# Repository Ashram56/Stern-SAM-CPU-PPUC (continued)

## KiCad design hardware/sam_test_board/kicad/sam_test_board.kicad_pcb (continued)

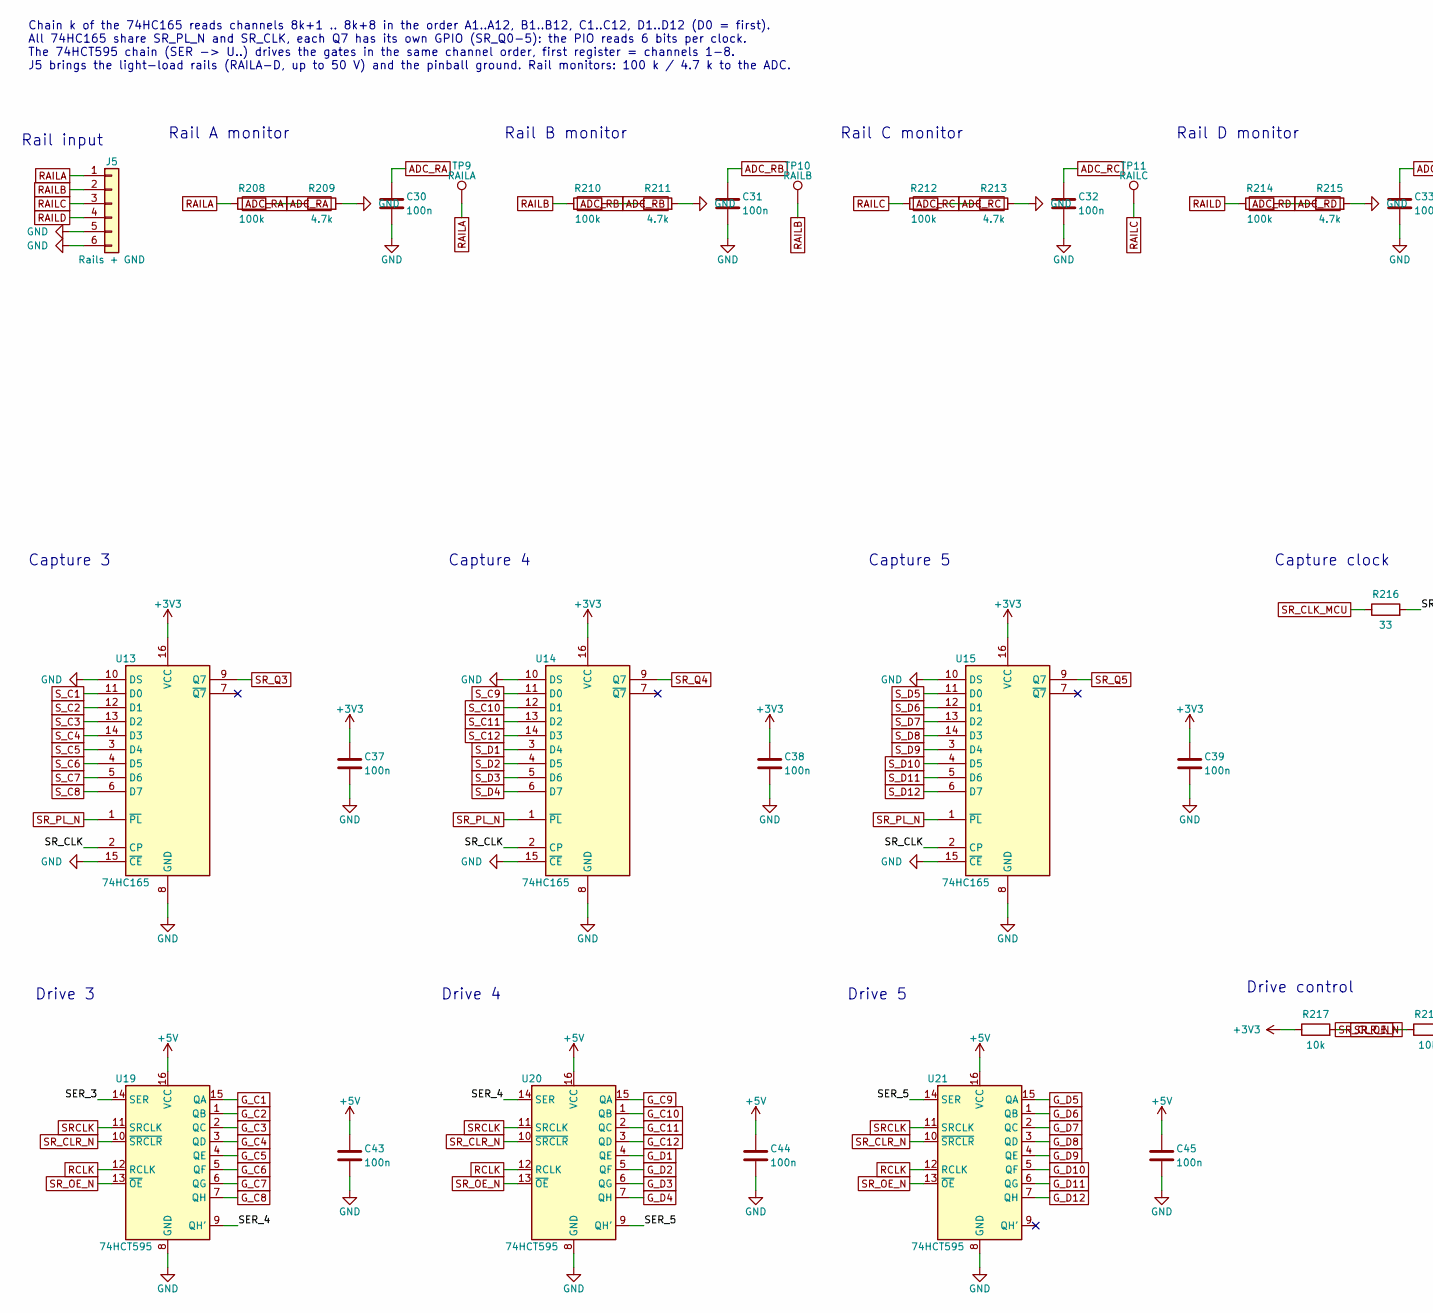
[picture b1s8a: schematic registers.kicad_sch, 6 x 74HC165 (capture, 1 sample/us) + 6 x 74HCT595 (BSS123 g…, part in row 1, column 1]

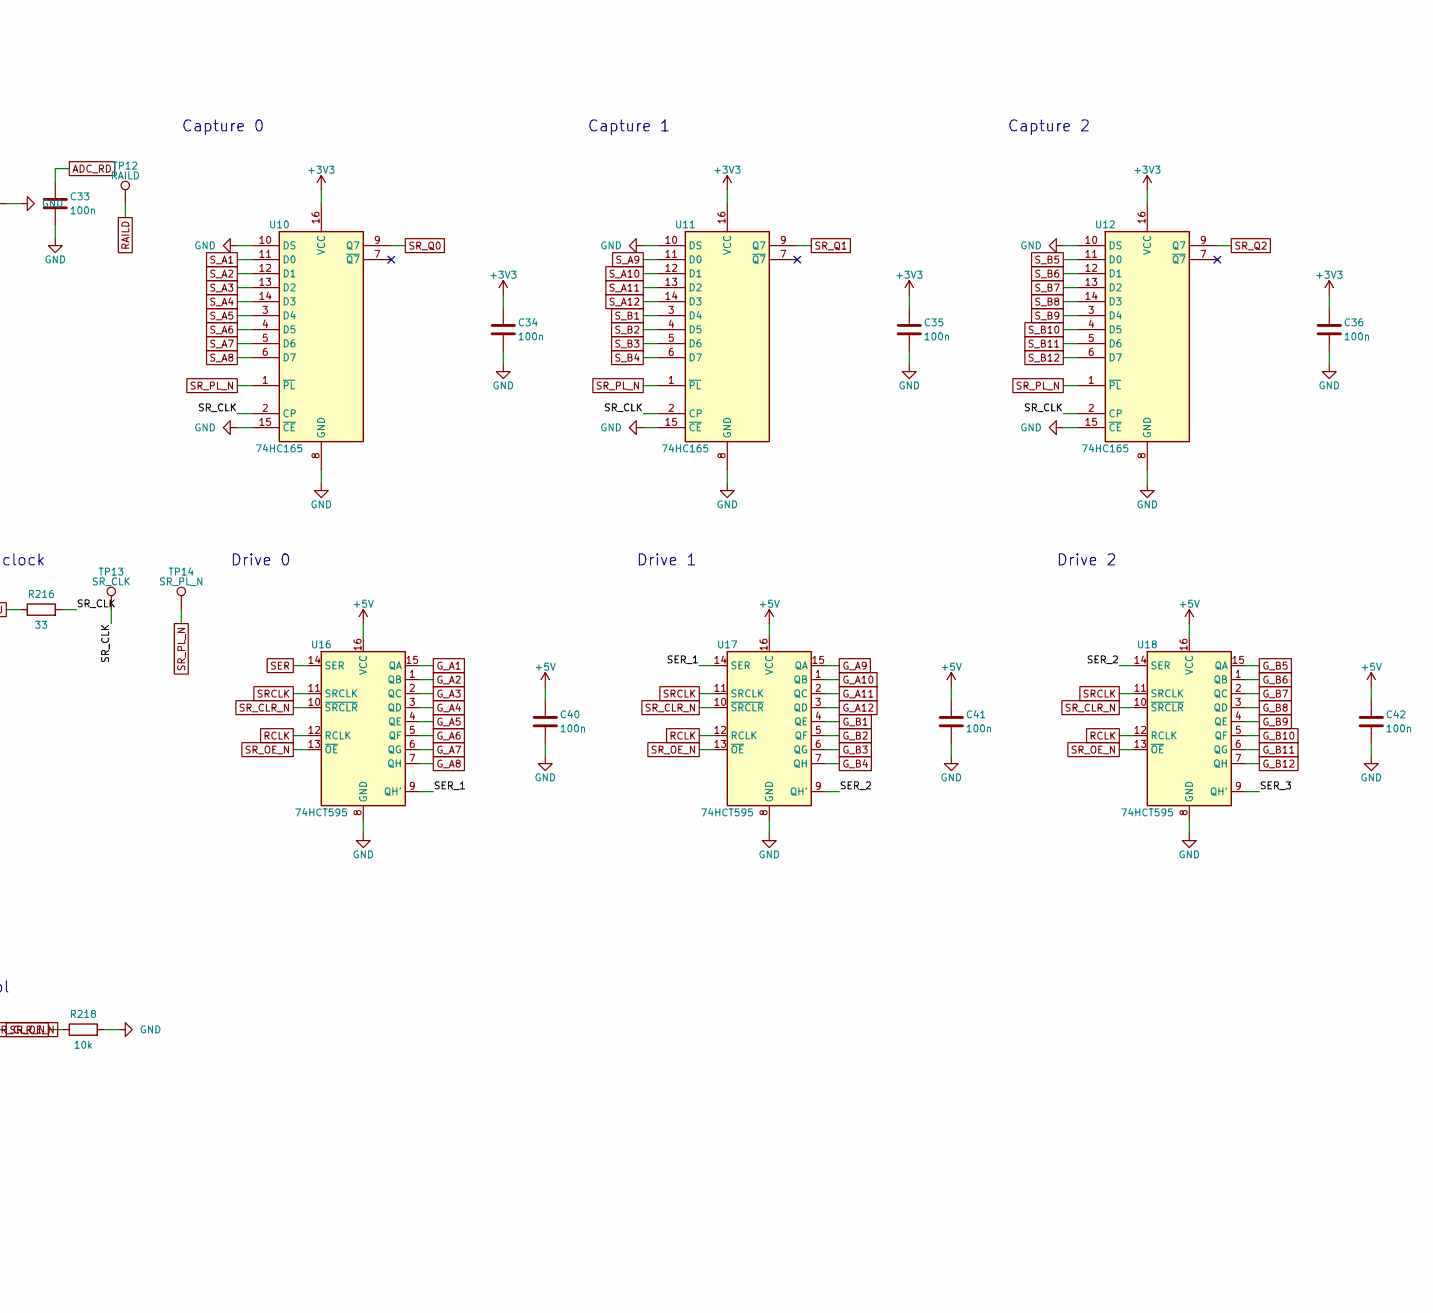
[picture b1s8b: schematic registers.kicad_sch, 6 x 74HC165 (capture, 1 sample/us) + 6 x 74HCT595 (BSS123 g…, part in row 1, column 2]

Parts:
C30, C31, C32, C33, C34, C35, C36, C37, C38, C39, C40, C41, C42, C43, C44, C45: 100n; C_0805_2012Metric
J5: Rails + GND; Molex_KK-396_A-41791-0006_1x06_P3.96mm_Vertical
R208, R210, R212, R214: 100k; R_0805_2012Metric
R209, R211, R213, R215: 4.7k; R_0805_2012Metric
R216: 33; R_0805_2012Metric
R217, R218: 10k; R_0805_2012Metric
TP9: RAILA; TestPoint_Pad_D1.5mm
TP10: RAILB; TestPoint_Pad_D1.5mm
TP11: RAILC; TestPoint_Pad_D1.5mm
TP12: RAILD; TestPoint_Pad_D1.5mm
TP13: SR_CLK; TestPoint_Pad_D1.5mm
TP14: SR_PL_N; TestPoint_Pad_D1.5mm
U10, U11, U12, U13, U14, U15: 74HC165; SOIC-16_3.9x9.9mm_P1.27mm
U16, U17, U18, U19, U20, U21: 74HCT595; SOIC-16_3.9x9.9mm_P1.27mm

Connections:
+3V3: C34.1, C35.1, C36.1, C37.1, C38.1, C39.1, R217.1, U10.16 (VCC), U11.16 (VCC), U12.16 (VCC), U13.16 (VCC), U14.16 (VCC), U15.16 (VCC); also elsewhere on the board
+5V: C40.1, C41.1, C42.1, C43.1, C44.1, C45.1, U16.16 (VCC), U17.16 (VCC), U18.16 (VCC), U19.16 (VCC), U20.16 (VCC), U21.16 (VCC); also elsewhere on the board
/Registers/SER_1: U16.9 (QH'), U17.14 (SER)
/Registers/SER_2: U17.9 (QH'), U18.14 (SER)
/Registers/SER_3: U18.9 (QH'), U19.14 (SER)
/Registers/SER_4: U19.9 (QH'), U20.14 (SER)
/Registers/SER_5: U20.9 (QH'), U21.14 (SER)
/Registers/SR_CLK: R216.2, TP13.1, U10.2 (CP), U11.2 (CP), U12.2 (CP), U13.2 (CP), U14.2 (CP), U15.2 (CP)
ADC_RA: C30.1, R208.2, R209.1; also elsewhere on the board
ADC_RB: C31.1, R210.2, R211.1; also elsewhere on the board
ADC_RC: C32.1, R212.2, R213.1; also elsewhere on the board
ADC_RD: C33.1, R214.2, R215.1; also elsewhere on the board
GND: C30.2, C31.2, C32.2, C33.2, C34.2, C35.2, C36.2, C37.2, C38.2, C39.2, C40.2, C41.2, C42.2, C43.2, C44.2, C45.2, J5.5, J5.6, R209.2, R211.2, R213.2, R215.2, R218.2, U10.8 (GND), U10.10 (DS), U10.15 (~CE), U11.8 (GND), U11.10 (DS), U11.15 (~CE), U12.8 (GND), U12.10 (DS), U12.15 (~CE), U13.8 (GND), U13.10 (DS), U13.15 (~CE), U14.8 (GND), U14.10 (DS), U14.15 (~CE), U15.8 (GND), U15.10 (DS), U15.15 (~CE), U16.8 (GND), U17.8 (GND), U18.8 (GND), U19.8 (GND), U20.8 (GND), U21.8 (GND); also elsewhere on the board
G_A1: U16.15 (QA); also elsewhere on the board
G_A2: U16.1 (QB); also elsewhere on the board
G_A3: U16.2 (QC); also elsewhere on the board
G_A4: U16.3 (QD); also elsewhere on the board
G_A5: U16.4 (QE); also elsewhere on the board
G_A6: U16.5 (QF); also elsewhere on the board
G_A7: U16.6 (QG); also elsewhere on the board
G_A8: U16.7 (QH); also elsewhere on the board
G_A9: U17.15 (QA); also elsewhere on the board
G_A10: U17.1 (QB); also elsewhere on the board
G_A11: U17.2 (QC); also elsewhere on the board
G_A12: U17.3 (QD); also elsewhere on the board
G_B1: U17.4 (QE); also elsewhere on the board
G_B2: U17.5 (QF); also elsewhere on the board
G_B3: U17.6 (QG); also elsewhere on the board
G_B4: U17.7 (QH); also elsewhere on the board
G_B5: U18.15 (QA); also elsewhere on the board
G_B6: U18.1 (QB); also elsewhere on the board
G_B7: U18.2 (QC); also elsewhere on the board
G_B8: U18.3 (QD); also elsewhere on the board
G_B9: U18.4 (QE); also elsewhere on the board
G_B10: U18.5 (QF); also elsewhere on the board
G_B11: U18.6 (QG); also elsewhere on the board
G_B12: U18.7 (QH); also elsewhere on the board
G_C1: U19.15 (QA); also elsewhere on the board
G_C2: U19.1 (QB); also elsewhere on the board
G_C3: U19.2 (QC); also elsewhere on the board
G_C4: U19.3 (QD); also elsewhere on the board
G_C5: U19.4 (QE); also elsewhere on the board
G_C6: U19.5 (QF); also elsewhere on the board
G_C7: U19.6 (QG); also elsewhere on the board
G_C8: U19.7 (QH); also elsewhere on the board
G_C9: U20.15 (QA); also elsewhere on the board
G_C10: U20.1 (QB); also elsewhere on the board
G_C11: U20.2 (QC); also elsewhere on the board
G_C12: U20.3 (QD); also elsewhere on the board
G_D1: U20.4 (QE); also elsewhere on the board
G_D2: U20.5 (QF); also elsewhere on the board
G_D3: U20.6 (QG); also elsewhere on the board
G_D4: U20.7 (QH); also elsewhere on the board
G_D5: U21.15 (QA); also elsewhere on the board
G_D6: U21.1 (QB); also elsewhere on the board
G_D7: U21.2 (QC); also elsewhere on the board
G_D8: U21.3 (QD); also elsewhere on the board
G_D9: U21.4 (QE); also elsewhere on the board
G_D10: U21.5 (QF); also elsewhere on the board
G_D11: U21.6 (QG); also elsewhere on the board
G_D12: U21.7 (QH); also elsewhere on the board
RAILA: J5.1, R208.1, TP9.1; also elsewhere on the board
RAILB: J5.2, R210.1, TP10.1; also elsewhere on the board
RAILC: J5.3, R212.1, TP11.1; also elsewhere on the board
RAILD: J5.4, R214.1, TP12.1; also elsewhere on the board
RCLK: U16.12 (RCLK), U17.12 (RCLK), U18.12 (RCLK), U19.12 (RCLK), U20.12 (RCLK), U21.12 (RCLK); also elsewhere on the board
SER: U16.14 (SER); also elsewhere on the board
SRCLK: U16.11 (SRCLK), U17.11 (SRCLK), U18.11 (SRCLK), U19.11 (SRCLK), U20.11 (SRCLK), U21.11 (SRCLK); also elsewhere on the board
SR_CLK_MCU: R216.1; also elsewhere on the board
SR_CLR_N: R218.1, U16.10 (~SRCLR), U17.10 (~SRCLR), U18.10 (~SRCLR), U19.10 (~SRCLR), U20.10 (~SRCLR), U21.10 (~SRCLR); also elsewhere on the board
SR_OE_N: R217.2, U16.13 (~OE), U17.13 (~OE), U18.13 (~OE), U19.13 (~OE), U20.13 (~OE), U21.13 (~OE); also elsewhere on the board
SR_PL_N: TP14.1, U10.1 (~PL), U11.1 (~PL), U12.1 (~PL), U13.1 (~PL), U14.1 (~PL), U15.1 (~PL); also elsewhere on the board
SR_Q0: U10.9 (Q7); also elsewhere on the board
SR_Q1: U11.9 (Q7); also elsewhere on the board
SR_Q2: U12.9 (Q7); also elsewhere on the board
SR_Q3: U13.9 (Q7); also elsewhere on the board
SR_Q4: U14.9 (Q7); also elsewhere on the board
SR_Q5: U15.9 (Q7); also elsewhere on the board
S_A1: U10.11 (D0); also elsewhere on the board
S_A2: U10.12 (D1); also elsewhere on the board
S_A3: U10.13 (D2); also elsewhere on the board
S_A4: U10.14 (D3); also elsewhere on the board
S_A5: U10.3 (D4); also elsewhere on the board
S_A6: U10.4 (D5); also elsewhere on the board
S_A7: U10.5 (D6); also elsewhere on the board
S_A8: U10.6 (D7); also elsewhere on the board
S_A9: U11.11 (D0); also elsewhere on the board
S_A10: U11.12 (D1); also elsewhere on the board
S_A11: U11.13 (D2); also elsewhere on the board
S_A12: U11.14 (D3); also elsewhere on the board
S_B1: U11.3 (D4); also elsewhere on the board
S_B2: U11.4 (D5); also elsewhere on the board
S_B3: U11.5 (D6); also elsewhere on the board
S_B4: U11.6 (D7); also elsewhere on the board
S_B5: U12.11 (D0); also elsewhere on the board
S_B6: U12.12 (D1); also elsewhere on the board
S_B7: U12.13 (D2); also elsewhere on the board
S_B8: U12.14 (D3); also elsewhere on the board
S_B9: U12.3 (D4); also elsewhere on the board
S_B10: U12.4 (D5); also elsewhere on the board
S_B11: U12.5 (D6); also elsewhere on the board
S_B12: U12.6 (D7); also elsewhere on the board
S_C1: U13.11 (D0); also elsewhere on the board
S_C2: U13.12 (D1); also elsewhere on the board
S_C3: U13.13 (D2); also elsewhere on the board
S_C4: U13.14 (D3); also elsewhere on the board
S_C5: U13.3 (D4); also elsewhere on the board
S_C6: U13.4 (D5); also elsewhere on the board
S_C7: U13.5 (D6); also elsewhere on the board
S_C8: U13.6 (D7); also elsewhere on the board
S_C9: U14.11 (D0); also elsewhere on the board
S_C10: U14.12 (D1); also elsewhere on the board
S_C11: U14.13 (D2); also elsewhere on the board
S_C12: U14.14 (D3); also elsewhere on the board
S_D1: U14.3 (D4); also elsewhere on the board
S_D2: U14.4 (D5); also elsewhere on the board
S_D3: U14.5 (D6); also elsewhere on the board
S_D4: U14.6 (D7); also elsewhere on the board
S_D5: U15.11 (D0); also elsewhere on the board
S_D6: U15.12 (D1); also elsewhere on the board
S_D7: U15.13 (D2); also elsewhere on the board
S_D8: U15.14 (D3); also elsewhere on the board
S_D9: U15.3 (D4); also elsewhere on the board
S_D10: U15.4 (D5); also elsewhere on the board
S_D11: U15.5 (D6); also elsewhere on the board
S_D12: U15.6 (D7); also elsewhere on the board

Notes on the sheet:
Chain k of the 74HC165 reads channels 8k+1 .. 8k+8 in the order A1..A12, B1..B12, C1..C12, D1..D12 (D0 = first). All 74HC165 share SR_PL_N and SR_CLK, each Q7 has its own GPIO (SR_Q0-5): the PIO reads 6 bits per clock. The 74HCT595 chain (SER -> U..) drives the gates in the same channel order, firs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
Rail input
Rail A monitor
Rail B monitor
Rail C monitor
Rail D monitor
Capture 0
Capture 1
Capture 2
Capture 3
Capture 4
Capture 5
Capture clock
Drive 0
Drive 1
Drive 2
Drive 3
Drive 4
Drive 5
Drive control

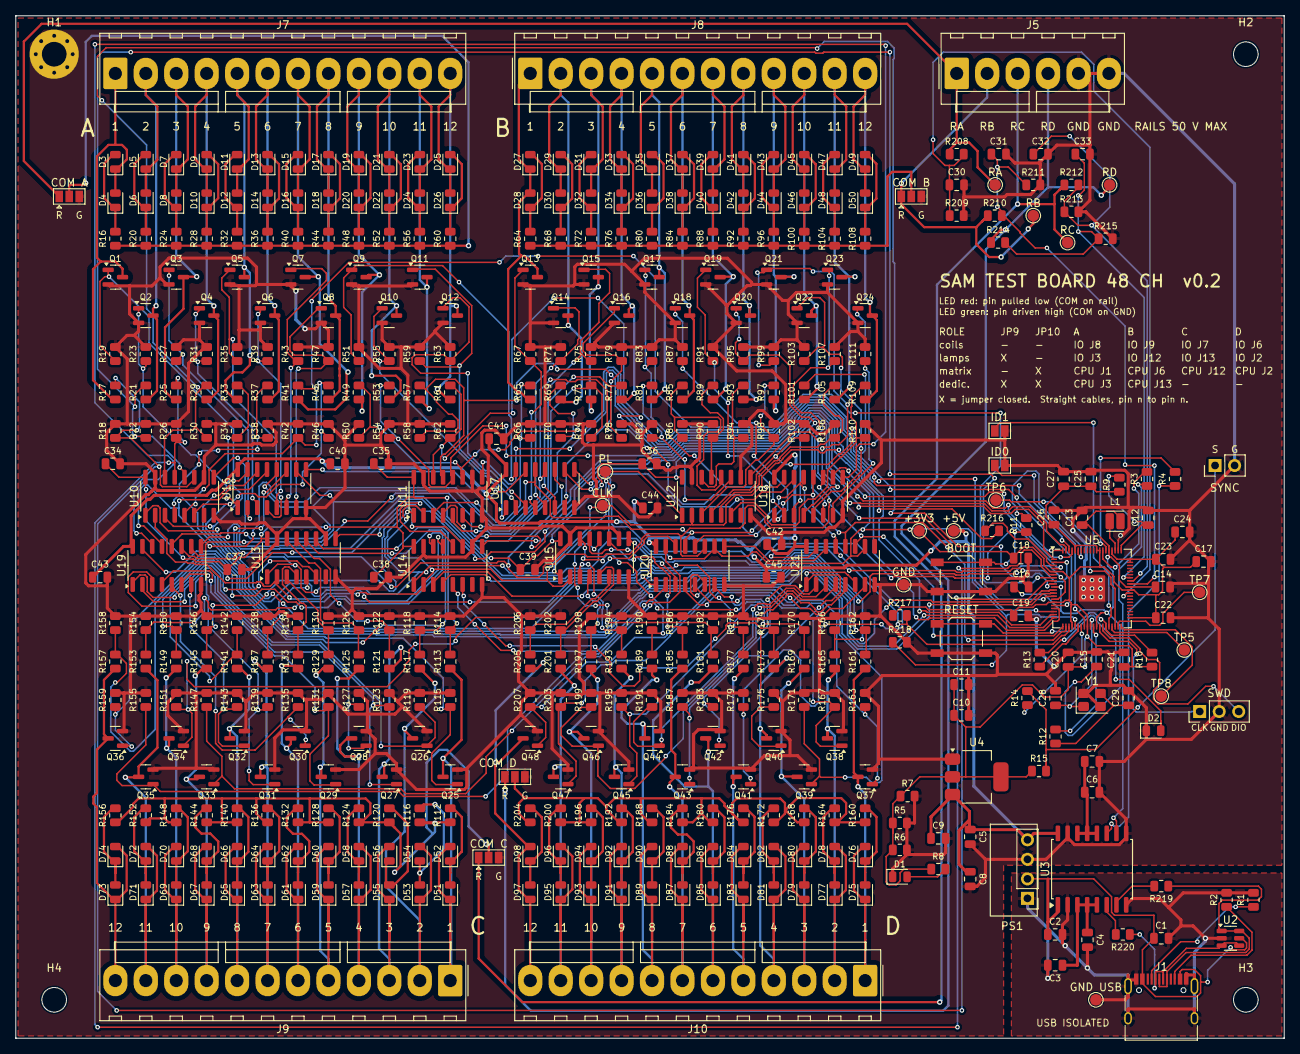
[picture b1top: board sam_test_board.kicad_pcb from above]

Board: 2 copper layers, 165.0 x 133.0 mm, 464 parts (0 on the bottom side), 262 nets.

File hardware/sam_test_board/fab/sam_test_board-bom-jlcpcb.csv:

Comment,Designator,Footprint,LCSC Part #
10u,"C1,C8,C9,C10",C_0805_2012Metric,C15850
100n,"C2,C4,C5,C7,C11,C14,C15,C16,C18,C19,C20,C21,C22,C23,C24,C25,C26,C27,C30,C31,C32,C33,C34,C35,C36,C37,C38,C39,C40,C41,C42,C43,C44,C45",C_0805_2012Metric,C49678
1u,"C3,C6",C_0805_2012Metric,C28323
4.7u,"C12,C13,C17",C_0805_2012Metric,C1779
15p,"C28,C29",C_0805_2012Metric,C63339
green,"D1,D4,D6,D8,D10,D12,D14,D16,D18,D20,D22,D24,D26,D28,D30,D32,D34,D36,D38,D40,D42,D44,D46,D48,D50,D52,D54,D56,D58,D60,D62,D64,D66,D68,D70,D72,D74,D76,D78,D80,D82,D84,D86,D88,D90,D92,D94,D96,D98",LED_0805_2012Metric,C2297
yellow,D2,LED_0805_2012Metric,C2296
red,"D3,D5,D7,D9,D11,D13,D15,D17,D19,D21,D23,D25,D27,D29,D31,D33,D35,D37,D39,D41,D43,D45,D47,D49,D51,D53,D55,D57,D59,D61,D63,D65,D67,D69,D71,D73,D75,D77,D79,D81,D83,D85,D87,D89,D91,D93,D95,D97",LED_0805_2012Metric,C84256
USB-C,J1,USB_C_Receptacle_HRO_TYPE-C-31-M-12,C165948
3.3u,L1,L_Cenker_CKCS201610,C167673
B0505S-1WR3,PS1,PinHeader_1x04_P2.54mm_Vertical,C2992394
BSS123,"Q1,Q2,Q3,Q4,Q5,Q6,Q7,Q8,Q9,Q10,Q11,Q12,Q13,Q14,Q15,Q16,Q17,Q18,Q19,Q20,Q21,Q22,Q23,Q24,Q25,Q26,Q27,Q28,Q29,Q30,Q31,Q32,Q33,Q34,Q35,Q36,Q37,Q38,Q39,Q40,Q41,Q42,Q43,Q44,Q45,Q46,Q47,Q48",SOT-23,C78962
5.1k,"R1,R2",R_0805_2012Metric,C27834
27,"R3,R4",R_0805_2012Metric,C17594
220,"R5,R6,R7",R_0805_2012Metric,C17557
1k,"R8,R11,R12,R13",R_0805_2012Metric,C17513
33,"R9,R216",R_0805_2012Metric,C17634
10k,"R10,R15,R217,R218",R_0805_2012Metric,C17414
330,R14,R_0805_2012Metric,C17630
33k,"R16,R20,R24,R28,R32,R36,R40,R44,R48,R52,R56,R60,R64,R68,R72,R76,R80,R84,R88,R92,R96,R100,R104,R108,R112,R116,R120,R124,R128,R132,R136,R140,R144,R148,R152,R156,R160,R164,R168,R172,R176,R180,R184,R188,R192,R196,R200,R204",R_0805_2012Metric,C17633
22k,"R17,R21,R25,R29,R33,R37,R41,R45,R49,R53,R57,R61",R_0805_2012Metric,C17560
47k,"R18,R22,R26,R30,R34,R38,R42,R46,R50,R54,R58,R62",R_0805_2012Metric,C17713
100k,"R19,R23,R27,R31,R35,R39,R43,R47,R51,R55,R59,R63,R65,R67,R69,R71,R73,R75,R77,R79,R81,R83,R85,R87,R89,R91,R93,R95,R97,R99,R101,R103,R105,R107,R109,R111,R113,R115,R117,R119,R121,R123,R125,R127,R129,R131,R133,R135,R137,R139,R141,R143,R145,R147,R149,R151,R153,R155,R157,R159,R161,R163,R165,R167,R169,R171,R173,R175,R177,R179,R181,R183,R185,R187,R189,R191,R193,R195,R197,R199,R201,R203,R205,R207,R208,R210,R212,R214",R_0805_2012Metric,C149504
220k,"R66,R70,R74,R78,R82,R86,R90,R94,R98,R102,R106,R110,R114,R118,R122,R126,R130,R134,R138,R142,R146,R150,R154,R158,R162,R166,R170,R174,R178,R182,R186,R190,R194,R198,R202,R206",R_0805_2012Metric,C17556
4.7k,"R209,R211,R213,R215",R_0805_2012Metric,C17673
RESET,SW1,SW_SPST_TL3342,C29780122
BOOTSEL,SW2,SW_SPST_TL3342,C29780122
USBLC6-2SC6,U2,SOT-23-6,C7519
ADuM3160BRWZ,U3,SOIC-16W_7.5x10.3mm_P1.27mm,C284149
NCP1117-3.3,U4,SOT-223-3_TabPin2,C26537
RP2354B,U5,QFN-80-1EP_10x10mm_P0.4mm_EP3.4x3.4mm,C39843328
74HC165,"U10,U11,U12,U13,U14,U15",SOIC-16_3.9x9.9mm_P1.27mm,C5613
74HCT595,"U16,U17,U18,U19,U20,U21",SOIC-16_3.9x9.9mm_P1.27mm,C282339
12MHz,Y1,Crystal_SMD_3225-4Pin_3.2x2.5mm,C133337

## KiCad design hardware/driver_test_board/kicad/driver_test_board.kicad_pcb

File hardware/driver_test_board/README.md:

# SAM driver output test board (banc de test des sorties driver)

R&D board that replaces the playfield and switch harnesses so the new CPU board can be tested without coils or
transistors at risk. Proposal and decisions: https://claude.ai/artifact/ANPhbTuL6jQy2aoAmm68Nv (Vincent, 2026-11-17).

- Plugs on the I/O Power Driver board 520-5249-00 outputs: J8, J9 (coils 1-16, 50 V), J7, J6 (coils/flashers 17-32,
  20 V), J10 (+50 V and ground; pin 1 = 24 VAC left open), J12 (10 lamp strobes), J13 (8 lamp columns, +18 V on
  pin 9 per the SAM schematic, JP1/JP2 swap pins 9 and 10), J2/J3 (aux data and strobes).
- Plugs on the CPU board switch inputs: J1 (8 strobes, read), J6/J12 (16 returns), J2/J3/J13 (24 dedicated), driven
  by 2N7002 from 74HCT595.
- Every output sees < 1 mA (47 k / 22 k + LED to its own rail), so a stuck output burns nothing. The 50 V and 20 V
  rails must be on: each output has a 1N4004 flyback diode to its rail on the driver board.
- 56 inputs sampled at 1 MHz by 7 x 74HC165 (PIO), aux lines direct on GPIO, rails on the ADC; RP2354B with USB
  isolated by an ADuM3160 and a 1 W B0505S.

## Files
- `kicad/`: KiCad 9 project: schematic draft 0.1 (ERC 0, `kicad/erc.rpt`) and the routed PCB
  `driver_test_board.kicad_pcb` (DRC report `kicad/drc.rpt`).
- `driver_test_board_schematic_v0.1.pdf`
- `fab/`: JLCPCB BOM and CPL (`driver_test_board-*-jlcpcb.csv`), copper renders. Gerbers come once routing is complete (`tools/make_fab.sh`).
- `firmware/`: RP2354B firmware (Pico SDK 2.2), see its README. `pc/sam_probe.py`: PC tool (pyserial).
- `tools/`: everything that produced the files above.
  - schematic: `build_dtb.py` + `design_dtb.py` (kigen/sexp/libs copied from `hardware/kicad/tools`);
  - PCB: `place_pcb.py` (placement from the netlist), `make_pro.py` (net classes), `finish_pcb.py`
    (Freerouting session import, GND / GND_USB pours), `jlc_bom.py` (BOM/CPL), `jlc_rotcheck.py` (JLC footprints).
  - From now on edit the KiCad files directly; the generators are the record of how the draft was made.

## PCB (draft 0.1)

- 250 x 150 mm, 2 layers, 1.6 mm. Four M3 holes in the corners (H1 = ground lug with pad).
- Edges: top = CPU J1, J6, J12, J2 + IO J2 (aux out); left = CPU J3, J13; right = IO J12, J13; bottom = IO J8, J9,
  J7, J6. Inside: IO J3 (aux strobes) and IO J10 (+50 V, ground). USB-C in the bottom-left corner, flush with the edge.
  All KK-396 friction ramps face the inside of the board.
- One column of parts per channel facing its pin (LED, pull-up, 220 k / 47 k divider), shift registers next to their
  channels, RP2354B in the middle with each decoupling capacitor at its supply pin.
- Net classes: HV (50 / 20 / 18 V lines and the LED nodes): 0.6 mm clearance (IPC-2221 B2, 31-50 V), 0.3 mm tracks.
  Default 0.2 mm / 0.15 mm (needed to leave the 0.4 mm pitch QFN). Power 0.4 mm.
- Isolation: GND_USB (PC side) covers x < 35.5 mm, y > 128 mm; a 0.5 mm strip with no track and no via separates it
  from GND, and the two pours are 1 mm apart. Only U3 (ADuM3160) and PS1 (B0505S) straddle it.
- Routed with Freerouting 1.9 (single thread: the multi-thread optimiser breaks clearances).

## JLCPCB

- 392 parts placed by JLC (391 SMD + PS1 B0505S through-hole), 31 LCSC codes, all in JLC stock on 2026-11-17 (RP2354B C39843328: 330, ADuM3160BRWZ-RL C284149:
  7984, B0505S-1WR3 C2992394: 34141, 3.3 uH FNR201610S3R3MT C167673 replaces the AOTA part, out of stock).
- Hand soldered: the 15 KK-396 headers (Molex 26-60-4090 / 4100 / 4120), SWD header, test points, solder jumpers.
- CPL rotations checked against the EasyEDA footprint of each LCSC part (`tools/jlc_rotcheck.py`): offsets in
  `jlc_bom.py` (SOIC and SOT-23-6 +270, 2N7002 and NCP1117 +180, B0505S +270 with its origin at the centre, USB-C
  origin shifted 1.575 mm). LEDs compared by K/A name (no offset), switch contacts 1-2 / 3-4 match the KiCad pads.

## Open
- **15 connections still to route by hand** (DRC `kicad/drc.rpt`, otherwise 0 clearance error): around the RP2354B
  (VREG_LX pin 63 to L1, VREG_AVDD pin 61, GND pin 62, +1V1, +3V3 pins 15/64, GP44 test point, ADC_V50, G_AUXO_P8,
  G_AUXO_P10, G_CSTB5, G_CSTB7) and the two J13 solder jumpers (JP1 pad 2 V18L, JP2 pad 2 LCOLX: Freerouting refuses
  the bridged pad). Then `tools/make_fab.sh` for the gerbers.
- Bring-up: firmware untested on hardware (see `firmware/README.md`).
- Silkscreen: reference designators overlap in the dense channel columns (cosmetic, DRC warnings only).

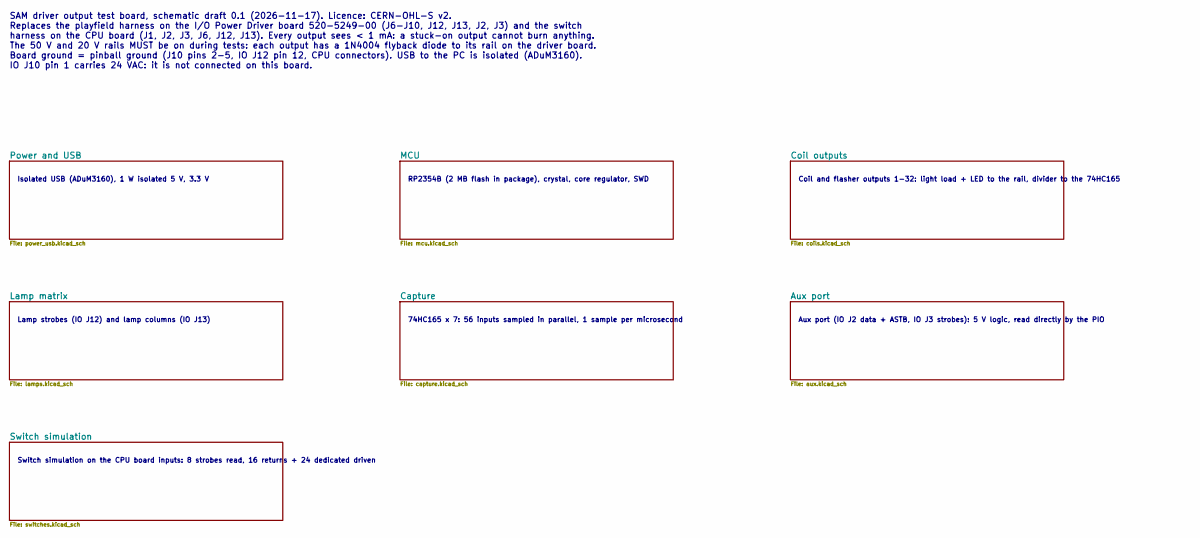
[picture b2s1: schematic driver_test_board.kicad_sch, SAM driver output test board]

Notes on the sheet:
Isolated USB (ADuM3160), 1 W isolated 5 V, 3.3 V
RP2354B (2 MB flash in package), crystal, core regulator, SWD
Coil and flasher outputs 1-32: light load + LED to the rail, divider to the 74HC165
Lamp strobes (IO J12) and lamp columns (IO J13)
74HC165 x 7: 56 inputs sampled in parallel, 1 sample per microsecond
Aux port (IO J2 data + ASTB, IO J3 strobes): 5 V logic, read directly by the PIO
Switch simulation on the CPU board inputs: 8 strobes read, 16 returns + 24 dedicated driven
SAM driver output test board, schematic draft 0.1 (2026-11-17). Licence: CERN-OHL-S v2. Replaces the playfield harness on the I/O Power Driver board 520-5249-00 (J6-J10, J12, J13, J2, J3) and the switch harness on the CPU board (J1, J2, J3, J6, J12, J13). Every output sees < 1 mA: a stuck-on output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

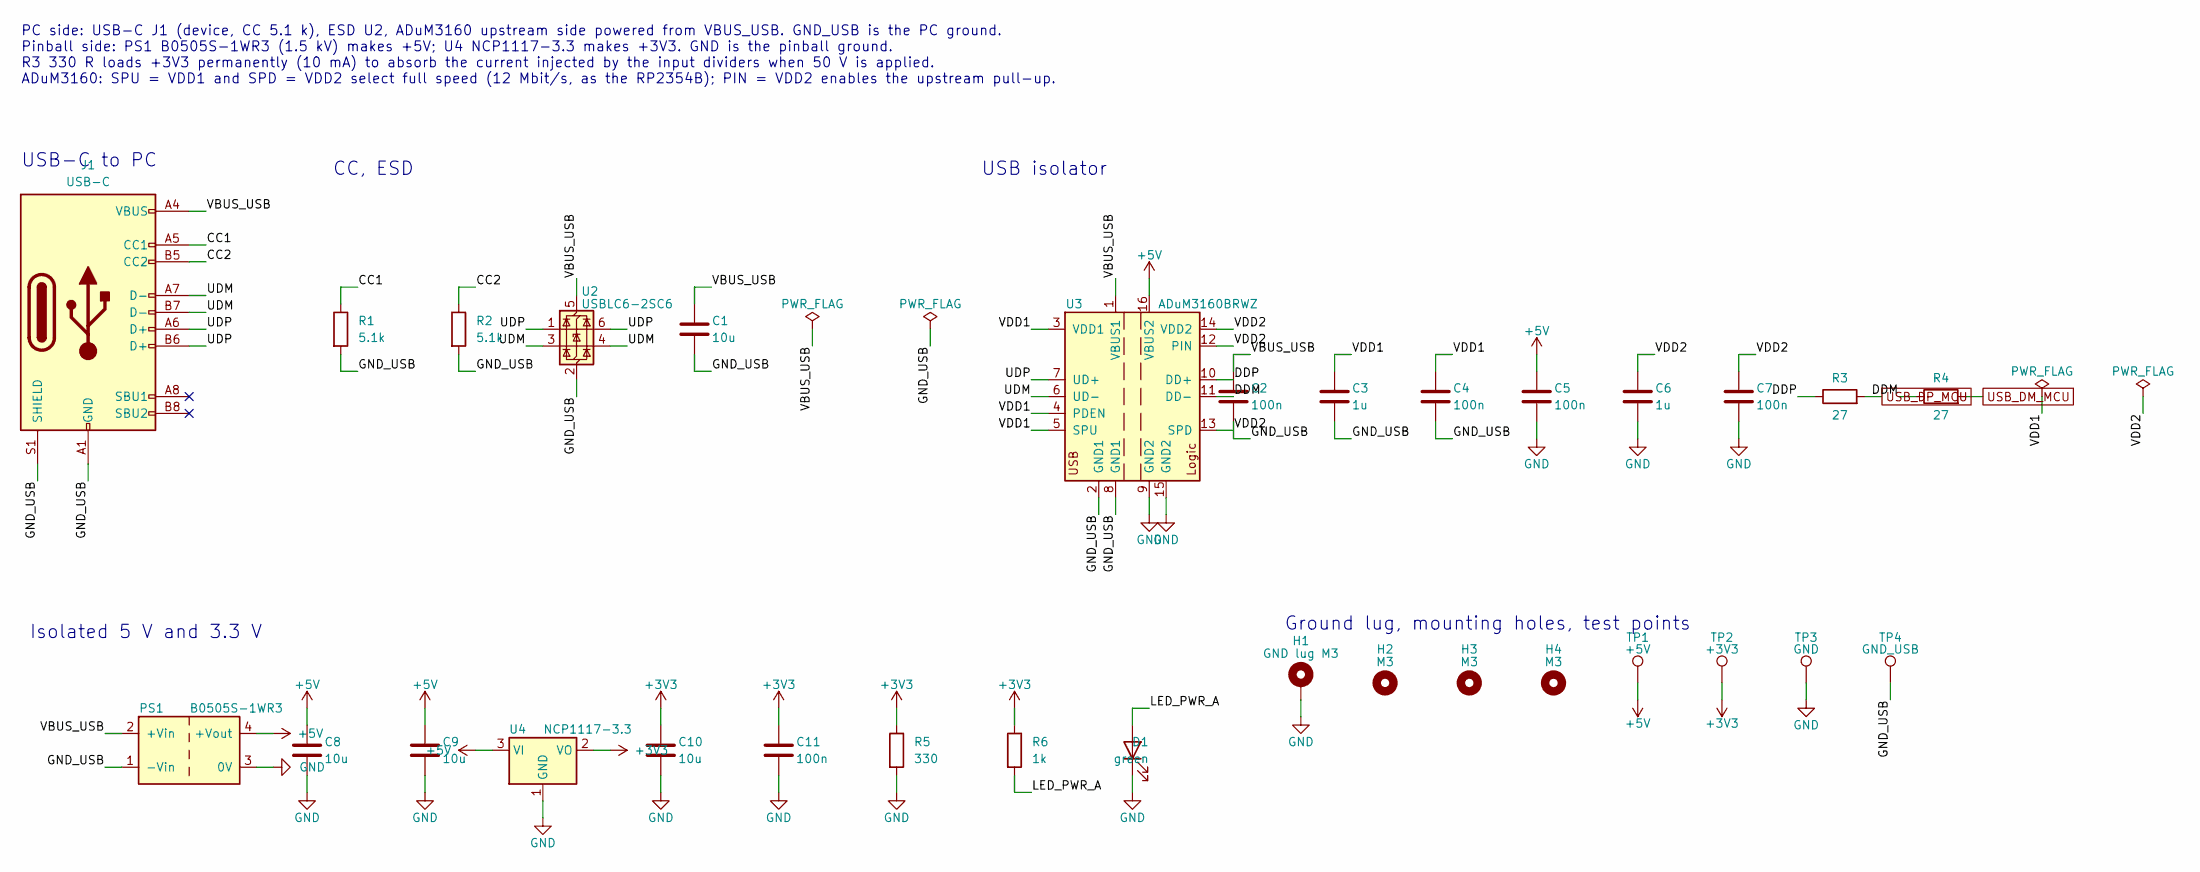
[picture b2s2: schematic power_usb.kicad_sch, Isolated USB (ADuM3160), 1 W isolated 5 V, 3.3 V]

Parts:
C1, C8, C9, C10: 10u; C_0805_2012Metric
C2, C4, C5, C7, C11: 100n; C_0805_2012Metric
C3, C6: 1u; C_0805_2012Metric
D1: green; LED_0805_2012Metric
H1: GND lug M3; MountingHole_3.2mm_M3_Pad_Via
H2, H3, H4: M3; MountingHole_3.2mm_M3
J1: USB-C; USB_C_Receptacle_HRO_TYPE-C-31-M-12
PS1: B0505S-1WR3; PinHeader_1x04_P2.54mm_Vertical
R1, R2: 5.1k; R_0805_2012Metric
R3, R4: 27; R_0805_2012Metric
R5: 330; R_0805_2012Metric
R6: 1k; R_0805_2012Metric
TP1: +5V; TestPoint_Pad_D1.5mm
TP2: +3V3; TestPoint_Pad_D1.5mm
TP3: GND; TestPoint_Pad_D1.5mm
TP4: GND_USB; TestPoint_Pad_D1.5mm
U2: USBLC6-2SC6; SOT-23-6
U3: ADuM3160BRWZ; SOIC-16W_7.5x10.3mm_P1.27mm
U4: NCP1117-3.3; SOT-223-3_TabPin2

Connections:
+3V3: C10.1, C11.1, R5.1, R6.1, TP2.1, U4.2 (VO); also elsewhere on the board
+5V: C5.1, C8.1, C9.1, PS1.4 (+Vout), TP1.1, U3.16 (VBUS2), U4.3 (VI); also elsewhere on the board
/Power and USB/CC1: J1.A5 (CC1), R1.1
/Power and USB/CC2: J1.B5 (CC2), R2.1
/Power and USB/DDM: R4.1, U3.11 (DD-)
/Power and USB/DDP: R3.1, U3.10 (DD+)
/Power and USB/LED_PWR_A: D1.2 (A), R6.2
/Power and USB/UDM: J1.A7 (D-), J1.B7 (D-), U2.3 (I/O2), U2.4 (I/O2), U3.6 (UD-)
/Power and USB/UDP: J1.A6 (D+), J1.B6 (D+), U2.1 (I/O1), U2.6 (I/O1), U3.7 (UD+)
/Power and USB/VBUS_USB: C1.1, C2.1, J1.A4 (VBUS), J1.A9 (VBUS), J1.B4 (VBUS), J1.B9 (VBUS), PS1.2 (+Vin), U2.5 (VBUS), U3.1 (VBUS1)
/Power and USB/VDD1: C3.1, C4.1, U3.3 (VDD1), U3.4 (PDEN), U3.5 (SPU)
GND: C5.2, C6.2, C7.2, C8.2, C9.2, C10.2, C11.2, D1.1 (K), H1.1, PS1.3 (0V), R5.2, TP3.1, U3.9 (GND2), U3.15 (GND2), U4.1 (GND); also elsewhere on the board
USB_DM_MCU: R4.2; also elsewhere on the board
USB_DP_MCU: R3.2; also elsewhere on the board

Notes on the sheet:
PC side: USB-C J1 (device, CC 5.1 k), ESD U2, ADuM3160 upstream side powered from VBUS_USB. GND_USB is the PC ground. Pinball side: PS1 B0505S-1WR3 (1.5 kV) makes +5V; U4 NCP1117-3.3 makes +3V3. GND is the pinball ground. R3 330 R loads +3V3 permanently (10 mA) to absorb the current injected by the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
USB-C to PC
CC, ESD
USB isolator
Isolated 5 V and 3.3 V
Ground lug, mounting holes, test points
